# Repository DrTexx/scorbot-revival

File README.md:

# Scorbot Revival Project
## Background
I received two robot arms during my mechanical engineering diploma. They were controlled via DOS and interfaced with DB9, DB25 and DB50 cables (standards that are since very outdated).

With the help of the my close friends from the CCHS hackerspace, I'm working on designing my own hardware and software to interface with the robots primary connector (a DB50 cable) without making any modifications to the robot arm's hardware itself.

Further, I hope to have the arms controllable via WiFi or other wireless means.

## Special thanks
- CCHS

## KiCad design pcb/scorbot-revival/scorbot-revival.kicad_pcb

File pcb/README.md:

# pcb

files related to pcb design and manufacturing

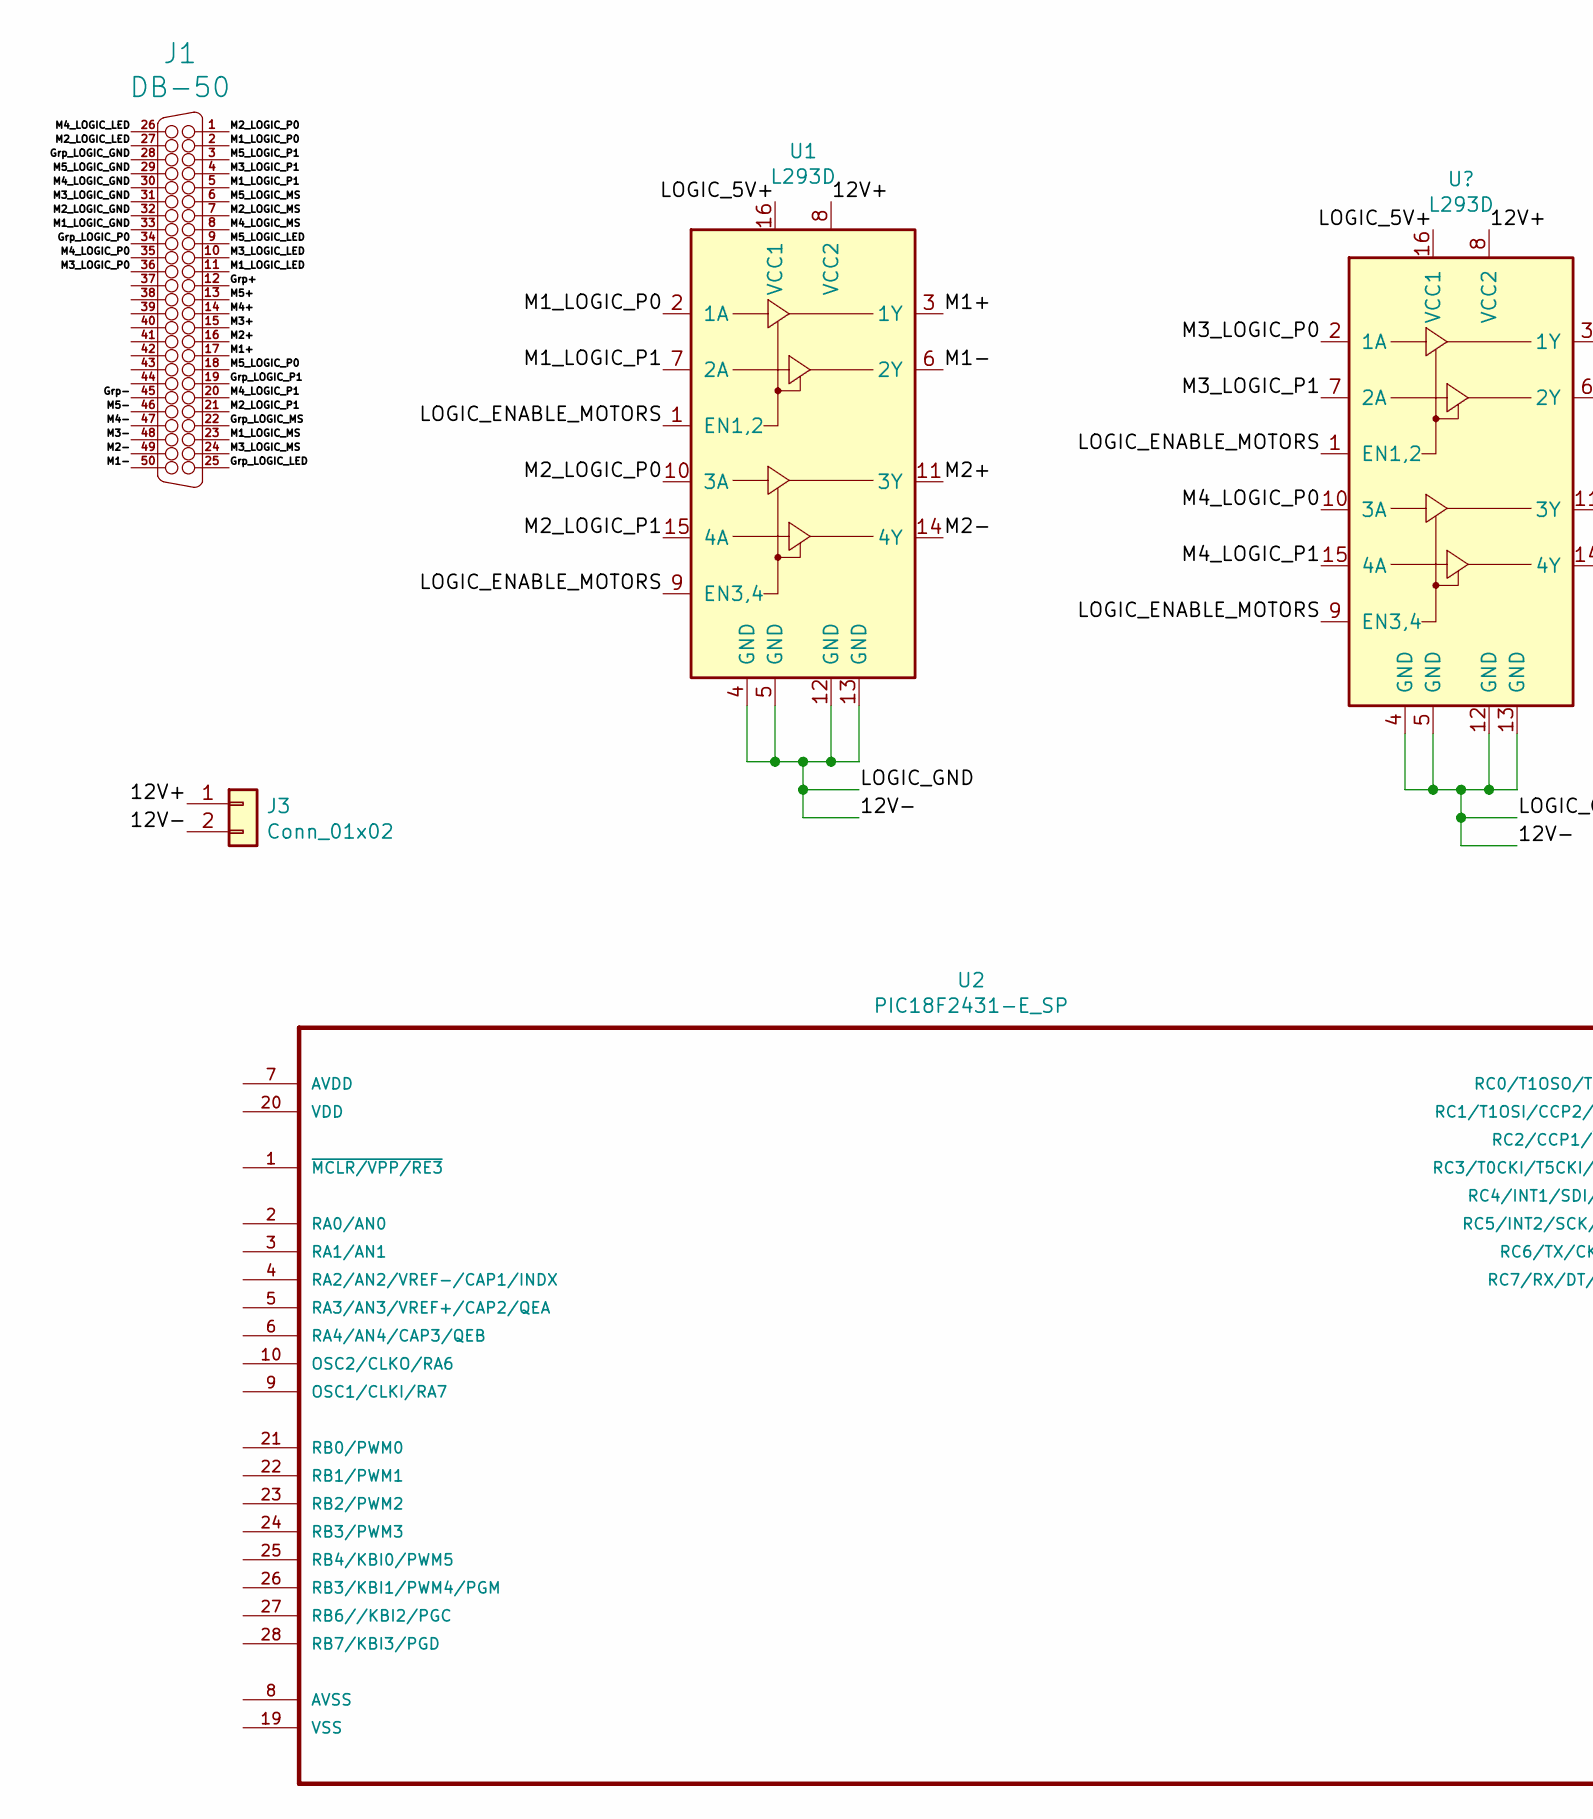
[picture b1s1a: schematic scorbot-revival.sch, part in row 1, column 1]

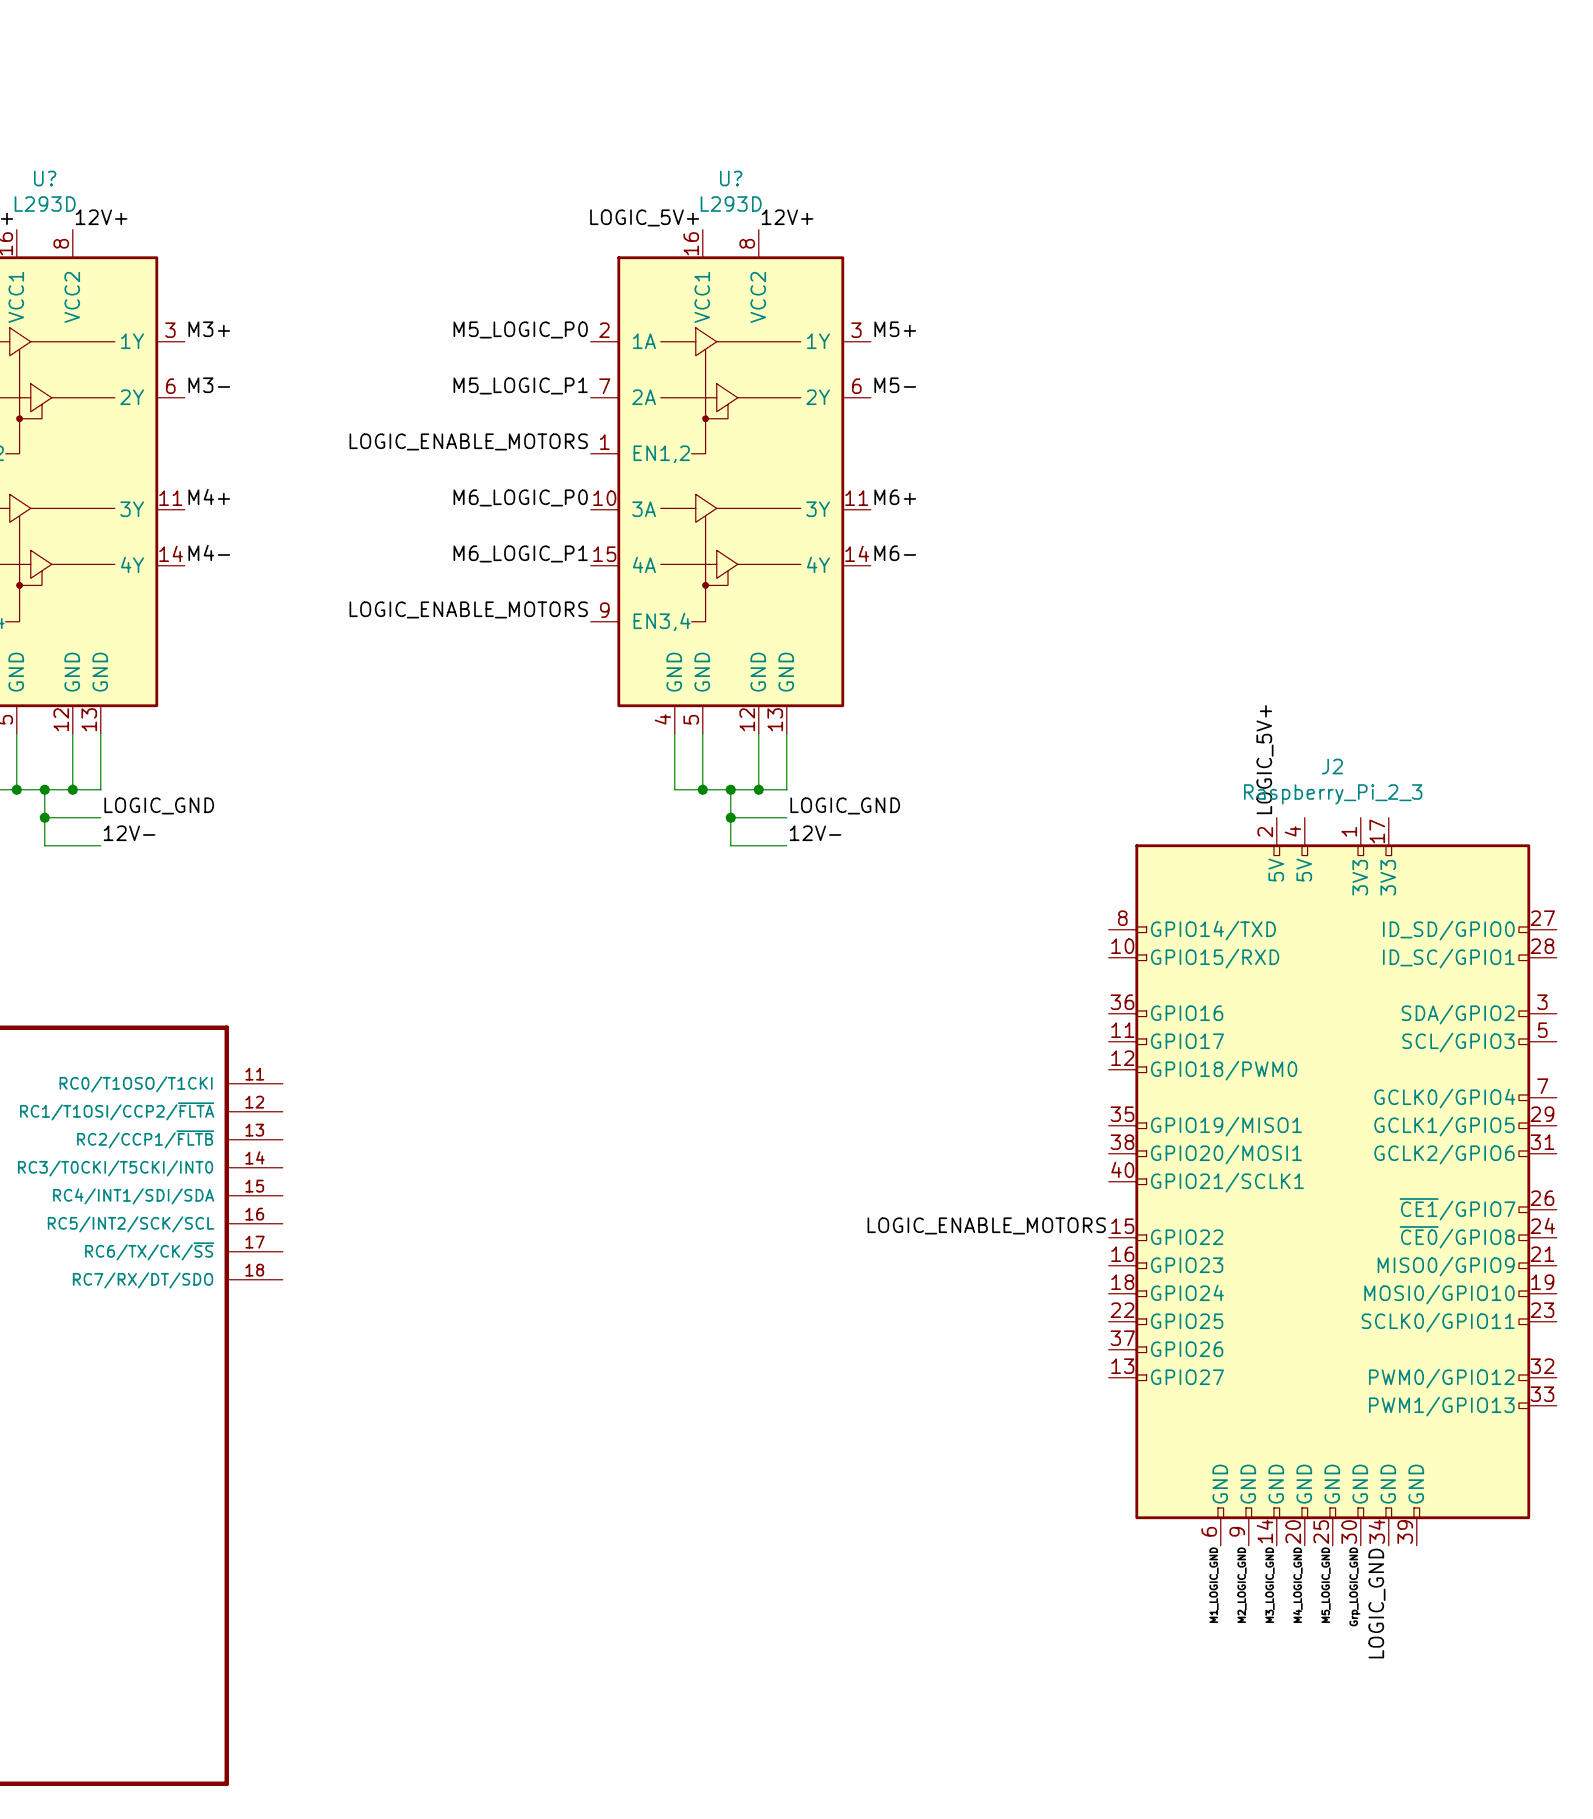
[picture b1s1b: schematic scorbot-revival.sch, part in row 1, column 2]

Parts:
J1: DB-50; 09665526612
J2: Raspberry_Pi_2_3; PinHeader_2x20_P2.54mm_Vertical
J3: Conn_01x02; BarrelJack_Horizontal
U1: L293D; DIP-16_W7.62mm
U2: PIC18F2431-E_SP; DIP-28_W7.62mm

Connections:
/12V+: J3.1, U1.8 (VCC2)
/12V-: J2.34 (GND), J3.2, U1.4 (GND), U1.5 (GND), U1.12 (GND), U1.13 (GND)
/Grp+: J1.12
/Grp-: J1.45
/Grp_LOGIC_GND: J1.28, J2.30 (GND)
/Grp_LOGIC_LED: J1.25
/Grp_LOGIC_MS: J1.22
/Grp_LOGIC_P0: J1.34
/Grp_LOGIC_P1: J1.19
/LOGIC_5V+: J2.2 (5V), U1.16 (VCC1)
/LOGIC_ENABLE_MOTORS: J2.15 (GPIO22), U1.1 (EN1,2), U1.9 (EN3,4)
/M1-: J1.50, U1.6 (2Y)
/M1_LOGIC_GND: J1.33, J2.6 (GND)
/M1_LOGIC_LED: J1.11
/M1_LOGIC_MS: J1.23
/M1_LOGIC_P0: J1.2, U1.2 (1A)
/M1_LOGIC_P1: J1.5, U1.7 (2A)
/M2+: J1.16, U1.11 (3Y)
/M2_LOGIC_GND: J1.32, J2.9 (GND)
/M2_LOGIC_LED: J1.27
/M2_LOGIC_MS: J1.7
/M2_LOGIC_P0: J1.1, U1.10 (3A)
/M2_LOGIC_P1: J1.21, U1.15 (4A)
/M3+: J1.15
/M3-: J1.48
/M3_LOGIC_GND: J1.31, J2.14 (GND)
/M3_LOGIC_LED: J1.10
/M3_LOGIC_MS: J1.24
/M3_LOGIC_P0: J1.36
/M3_LOGIC_P1: J1.4
/M4+: J1.14
/M4-: J1.47
/M4_LOGIC_GND: J1.30, J2.20 (GND)
/M4_LOGIC_LED: J1.26
/M4_LOGIC_MS: J1.8
/M4_LOGIC_P0: J1.35
/M4_LOGIC_P1: J1.20
/M5+: J1.13
/M5-: J1.46
/M5_LOGIC_GND: J1.29, J2.25 (GND)
/M5_LOGIC_LED: J1.9
/M5_LOGIC_MS: J1.6
/M5_LOGIC_P0: J1.18
/M5_LOGIC_P1: J1.3

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
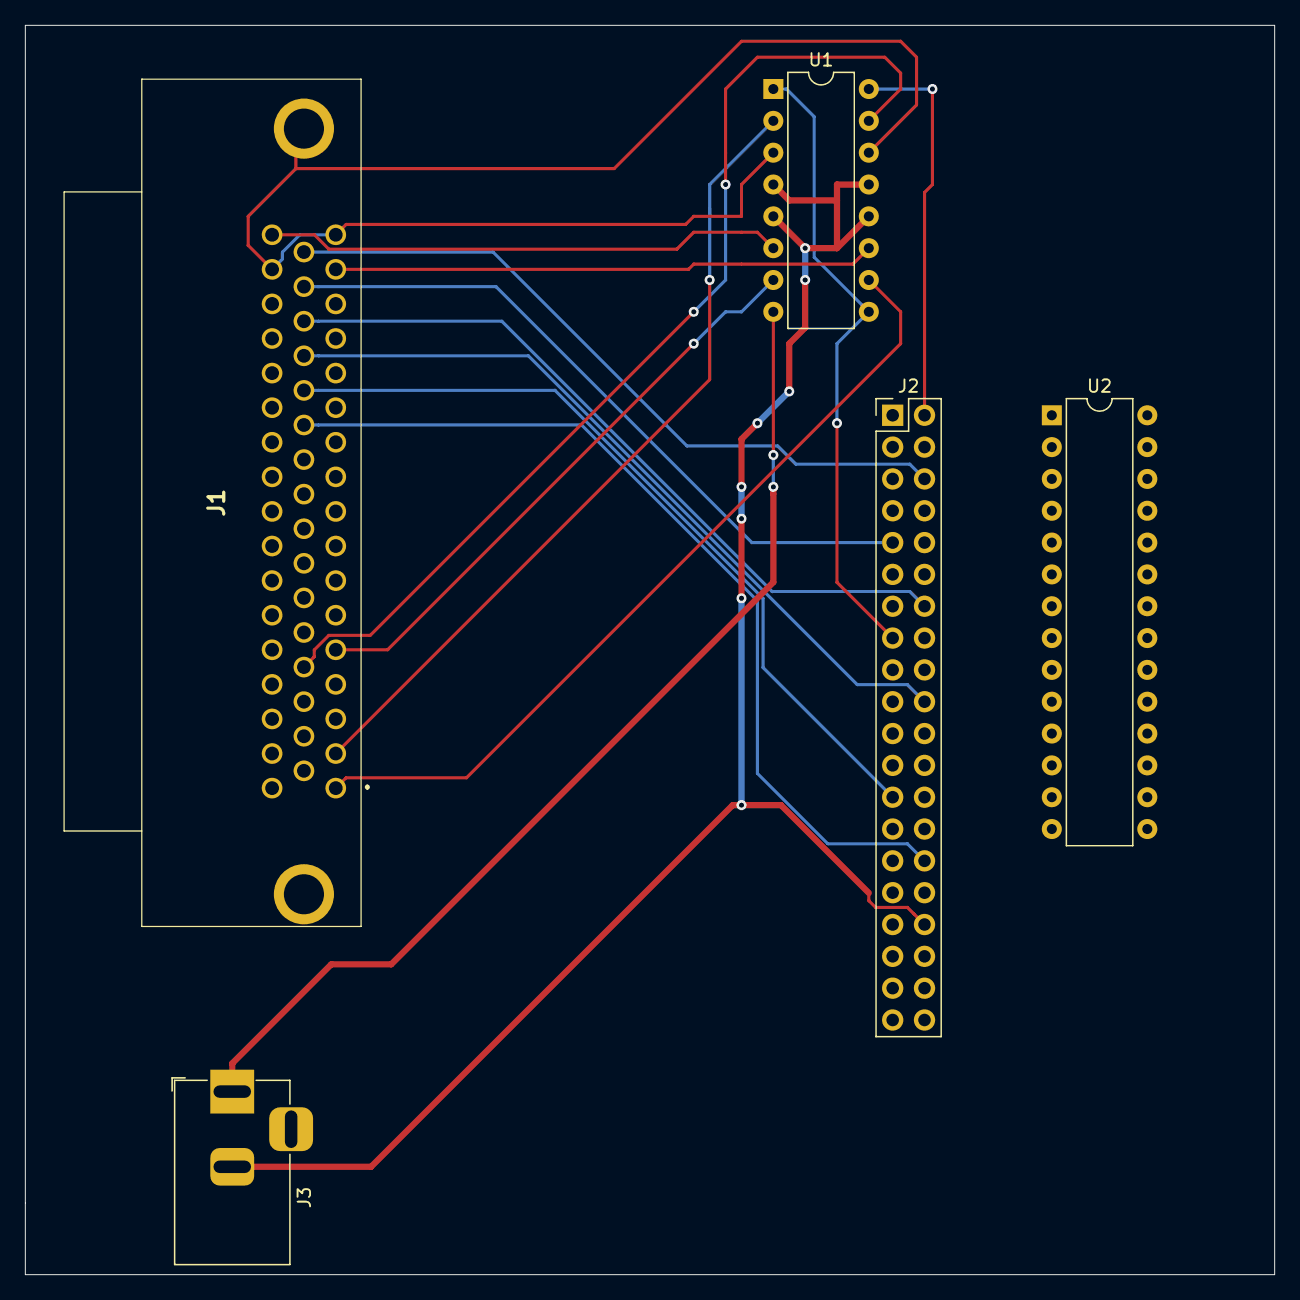
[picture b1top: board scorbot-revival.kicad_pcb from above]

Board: 2 copper layers, 99.7 x 99.7 mm, 5 parts (0 on the bottom side), 17 nets.

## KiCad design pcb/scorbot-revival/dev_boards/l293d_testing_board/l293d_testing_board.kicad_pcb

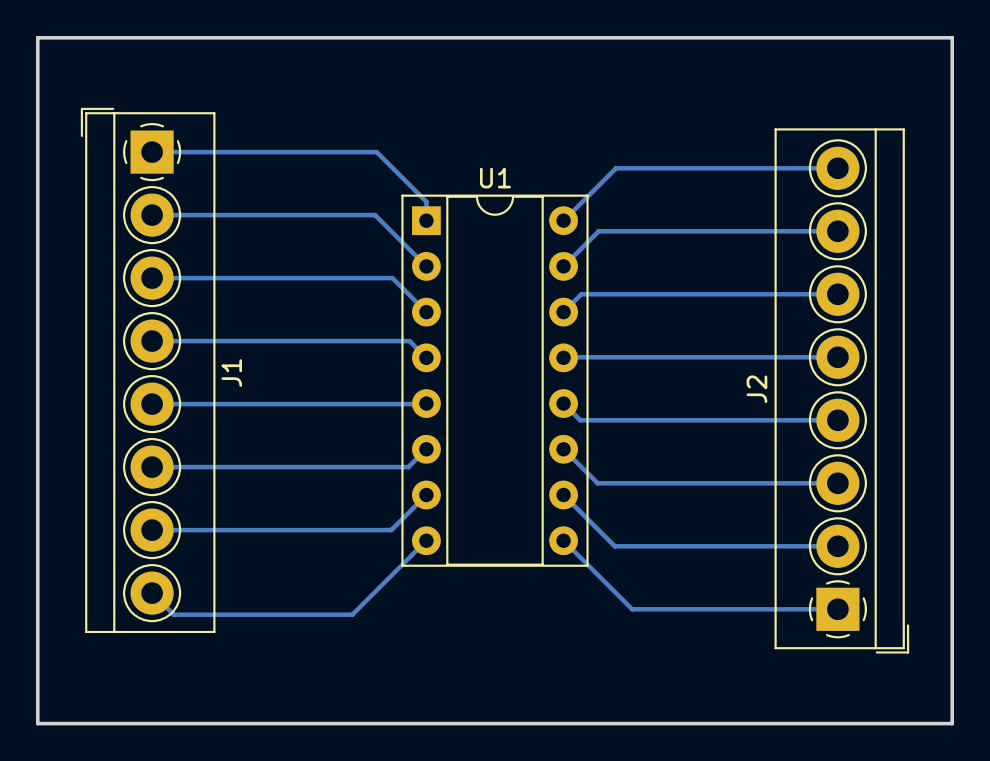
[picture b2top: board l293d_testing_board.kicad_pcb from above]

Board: 2 copper layers, 50.8 x 38.1 mm, 3 parts (0 on the bottom side), 16 nets.

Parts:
J1, J2: Screw_Terminal_01x08; TerminalBlock_4Ucon_1x08_P3.50mm_Horizontal
U1: L293D; DIP-16_W7.62mm_Socket

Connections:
unnamed: J1.1, U1.1
unnamed: J1.2, U1.2
unnamed: J1.3, U1.3
unnamed: J1.4, U1.4
unnamed: J1.5, U1.5
unnamed: J1.6, U1.6
unnamed: J1.7, U1.7
unnamed: J1.8, U1.8
unnamed: J2.1, U1.9
unnamed: J2.2, U1.10
unnamed: J2.3, U1.11
unnamed: J2.4, U1.12
unnamed: J2.5, U1.13
unnamed: J2.6, U1.14
unnamed: J2.7, U1.15
unnamed: J2.8, U1.16

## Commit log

2019-06-25 Initial commit - part 2
2019-06-25 [readme] updated
2019-06-25 remove unnecessary header file
2019-06-25 add .gitignore
2019-06-25 [readme] fixed typo
2019-06-25 updated gitignore
2019-06-26 add hardware classes
2019-06-26 Include hardware
2019-06-26 create hardware objects
2019-06-26 additional comment
2019-06-26 movement demo in it's own function
    (also removed some old commented out code)
2019-07-03 Give Motor class a constructor
2019-07-05 Motor pins now defined by a constant
2019-07-05 remove unused objects
2019-07-05 remove motor 2 pins
2019-07-05 change build environment to ESP32
2019-07-05 change motor pins to ESP32 pins
2019-07-05 add blink_led function
2019-07-05 change baud to match esp32 hardware
2019-07-05 commented out call for blink_led function
2019-07-05 fix a naming error in blink_led
2019-07-05 compiled code
2019-11-26 reorganise directory structure
2019-11-26 lol whoops
2019-11-26 move cpp to it's own directory
2019-11-27 create axis class
2019-11-28 add readme to design/STLS
2019-11-29 add heaps of readmes to explain directory structure to repo explorers
2019-11-29 [design component] add step file of DB50_F connector
2019-11-29 [design component] add original zip package for scorbot assembly
2019-11-29 [pcb] add inital pcb files
2019-11-29 [pcb] added labels to DB50 connector in schematic
2019-11-29 [pcb] add PIC16CE625-04I to schematic + pcbnew
2019-11-29 [pcb] replace old PIC with PIC18F2431-E_SP
2019-11-29 [code] add PID code example
2019-11-29 [code] add pid media
2019-11-29 [pcb] update schematic connections
2019-11-29 [pcb] pcbnew updates
2019-12-01 finished trace conections
    added trace and simplifyed
2019-12-10 Added more L293Ds to net
